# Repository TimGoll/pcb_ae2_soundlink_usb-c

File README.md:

# Bose Wireless AE2 Soundlink USB Type-C Conversion

A few months after the warranty expired one of the contacts in the USB receptable broke of. This made it impossible for me to charge the device. Since there were no replacement parts available, I wanted to fix it by myself. One possible solution was to just replace the receptacle on the PCB, but I wanted to use replace the PCB completely, because these headphones were my last remaining micro USB device.

_(The original PCB with the broken micro USB receptacle)_

After desoldering the PCB I got to work. First I traced the outline of the original PCB, then I enlarged it to fit the new receptacle. Over the course of a few iterations I modified the outline in a way that it perfectly fits inside the housing.

_(The formfactor design process; 3D printing helped with the outline verification)_

After designing the PCB it arrived a few days later in much greater quantity then ordered. I chose the thickness to be as thin as possible, 0.8mm in this case.

_(More PCBs then I have headphones)_

The assembly itself was rather straight forward.

_(The assembled PCB)_

The original wires were reused when connecting the PCB to the mainboard. Since I accidentally mirrored the pinout, I had to cross the wires (as can be seen on the right image). This however didn't cause any troubles.

_(The new PCB placed inside the housing, it fits perfectly)_

One modification to the housing has to be done before it can be closed again. The new receptacle is longer then the old one. Therefore the cutout has to be enlarged. This was a fairly easy task with a sharp knife.

_(The closed modified housing, the receptacle can be seen)_

## Used USB Receptacle

I used [these receptacles](https://www.we-online.com/katalog/de/COM_3_1_THR_SMT_TYPE_C_RECEPTACLE_HORIZONTAL) from Wuerth Electronics for my board. You should order the same (or similar) to have a matching footprint.

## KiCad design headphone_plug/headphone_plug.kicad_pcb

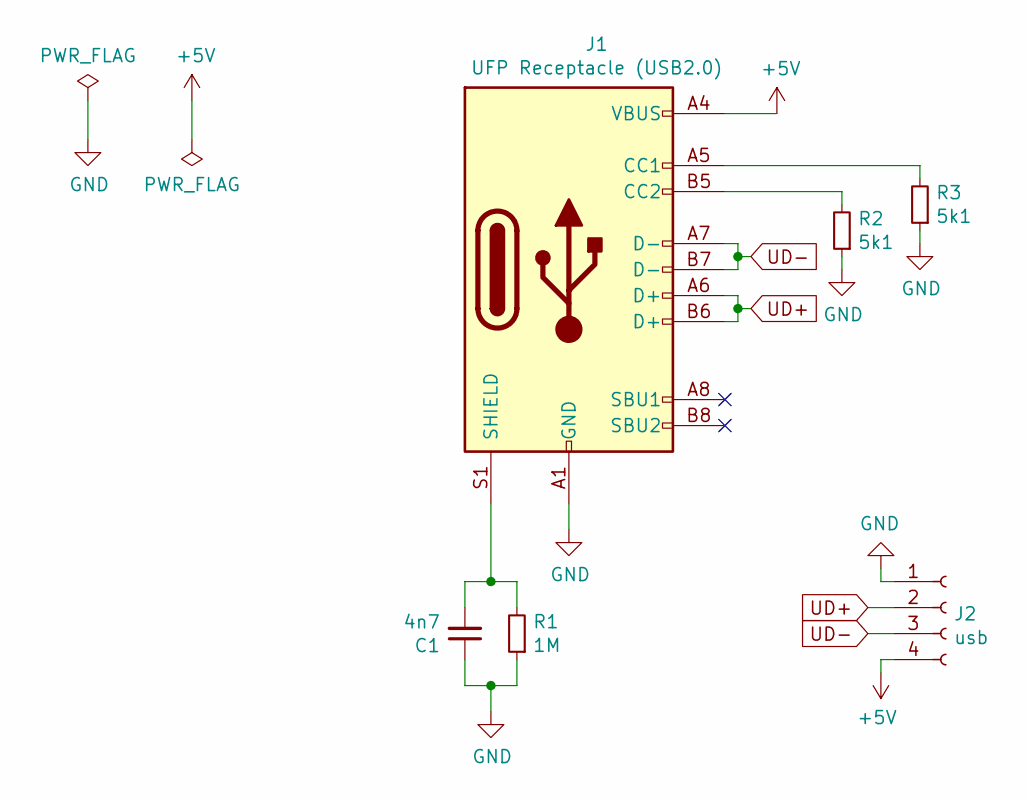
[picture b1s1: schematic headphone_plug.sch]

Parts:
C1: 4n7; C_0805_2012Metric_Pad1.15x1.40mm_HandSolder
J1: UFP Receptacle (USB2.0); USB_C_Receptacle_Würth
J2: usb; pads_01x04
R1: 1M; R_0805_2012Metric_Pad1.15x1.40mm_HandSolder
R2, R3: 5k1; R_0805_2012Metric_Pad1.15x1.40mm_HandSolder

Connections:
+5V: J1.A4 (VBUS), J1.A9 (VBUS), J1.B4 (VBUS), J1.B9 (VBUS), J2.4
GND: C1.1, J1.A1 (GND), J1.A12 (GND), J1.B1 (GND), J1.B12 (GND), J2.1, R1.1, R2.1, R3.1
unnamed: C1.2, J1.S1 (SHIELD), R1.2
unnamed: J1.A5 (CC1), R3.2
unnamed: J1.B5 (CC2), R2.2
UD+: J1.A6 (D+), J1.B6 (D+), J2.2
UD-: J1.A7 (D-), J1.B7 (D-), J2.3

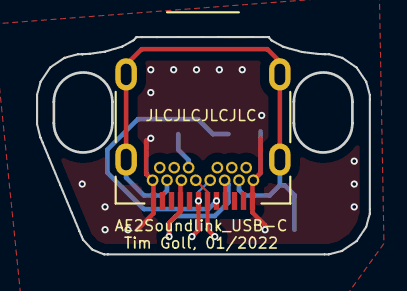
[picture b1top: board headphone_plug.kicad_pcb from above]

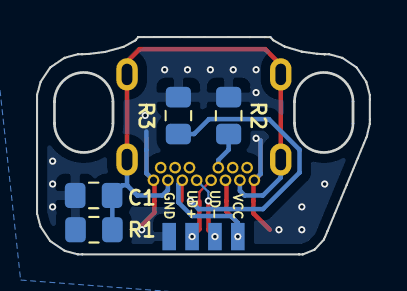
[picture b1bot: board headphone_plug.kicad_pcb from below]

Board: 2 copper layers, 18.5 x 12.0 mm, 6 parts (5 on the bottom side), 7 nets.

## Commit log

2022-01-04 added pcb
2022-01-04 updated holes
2022-02-15 added project description
